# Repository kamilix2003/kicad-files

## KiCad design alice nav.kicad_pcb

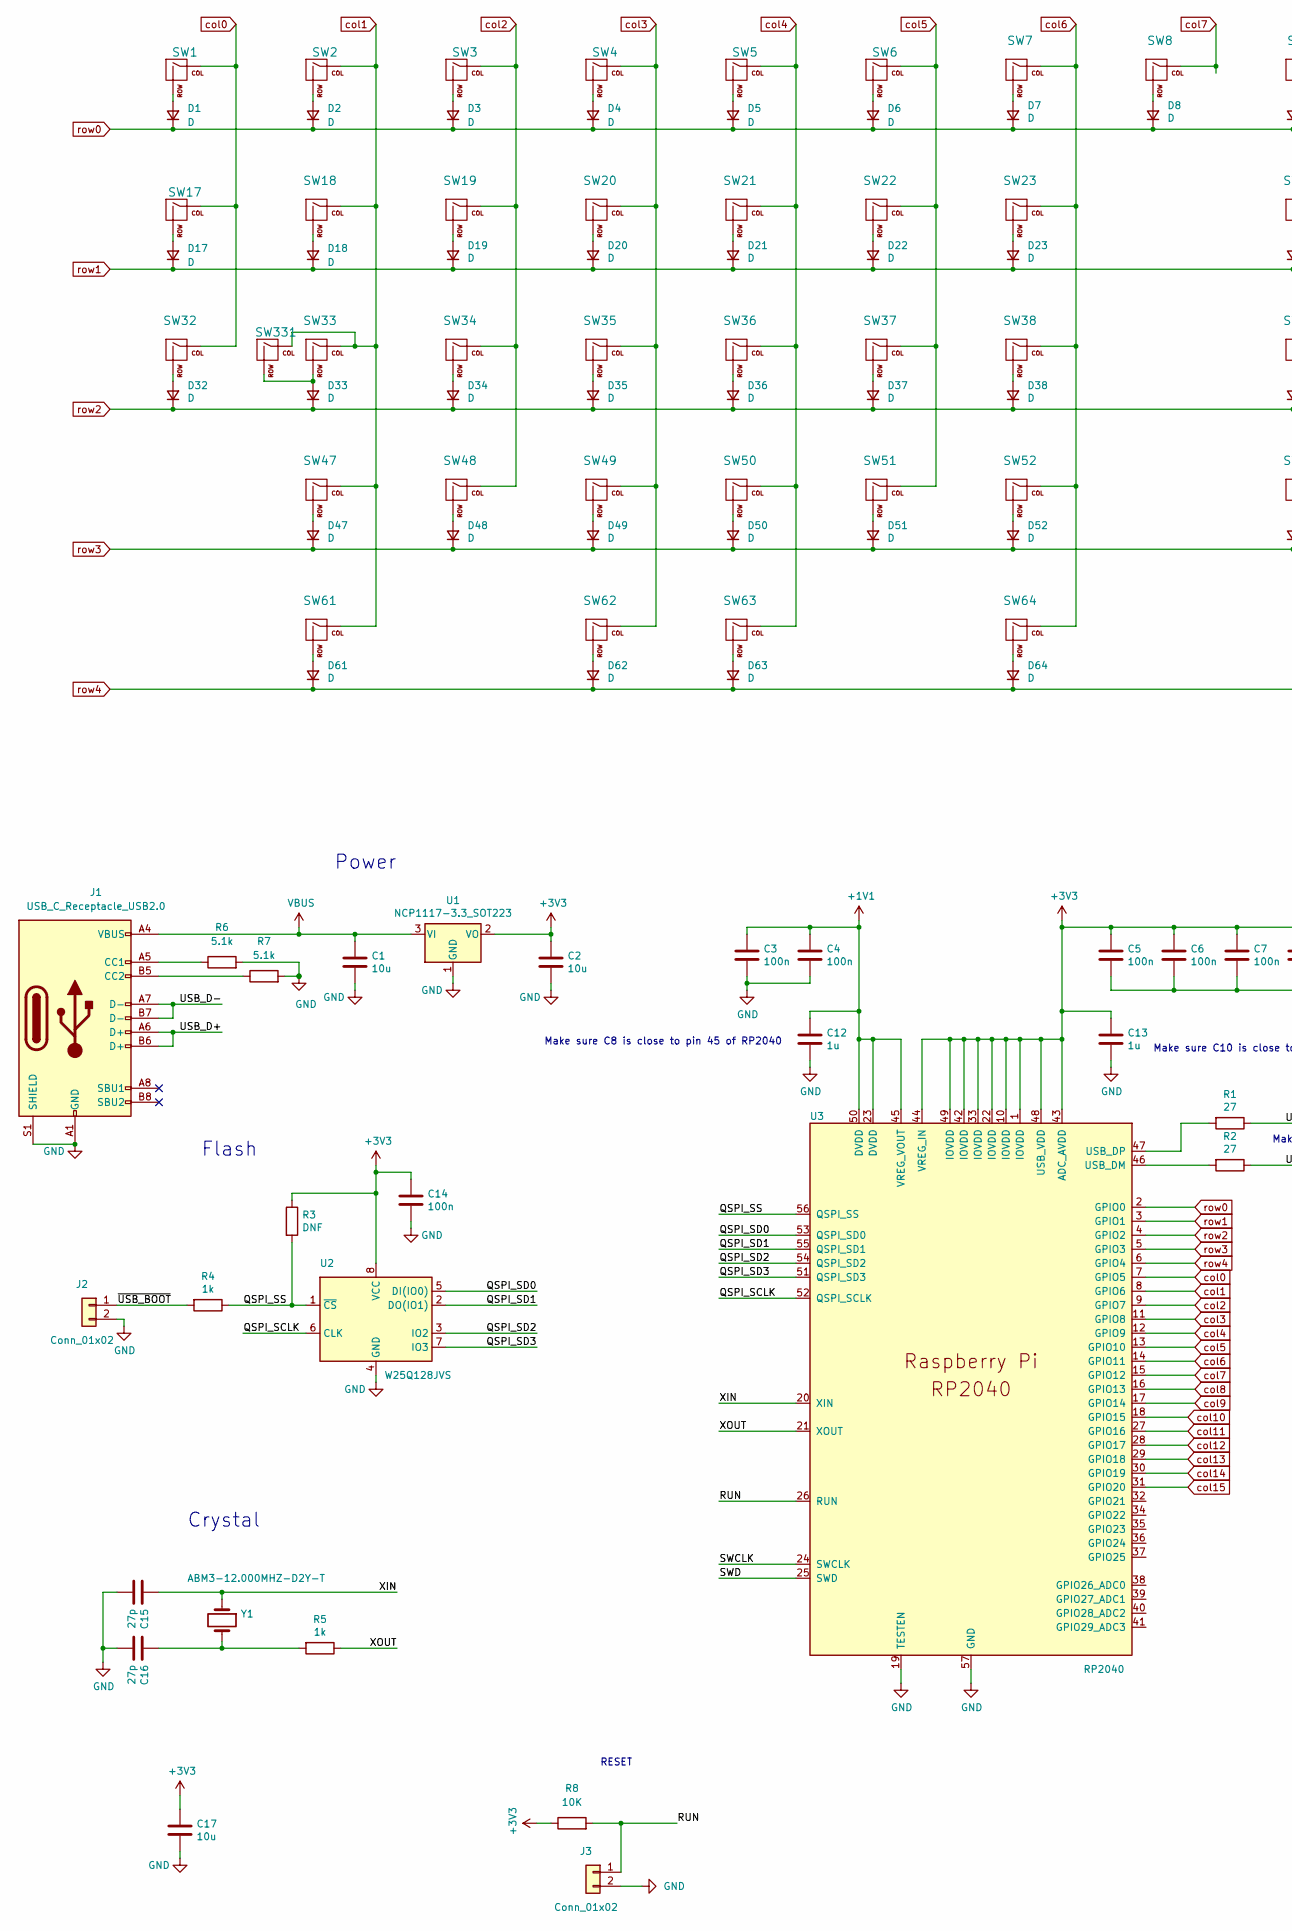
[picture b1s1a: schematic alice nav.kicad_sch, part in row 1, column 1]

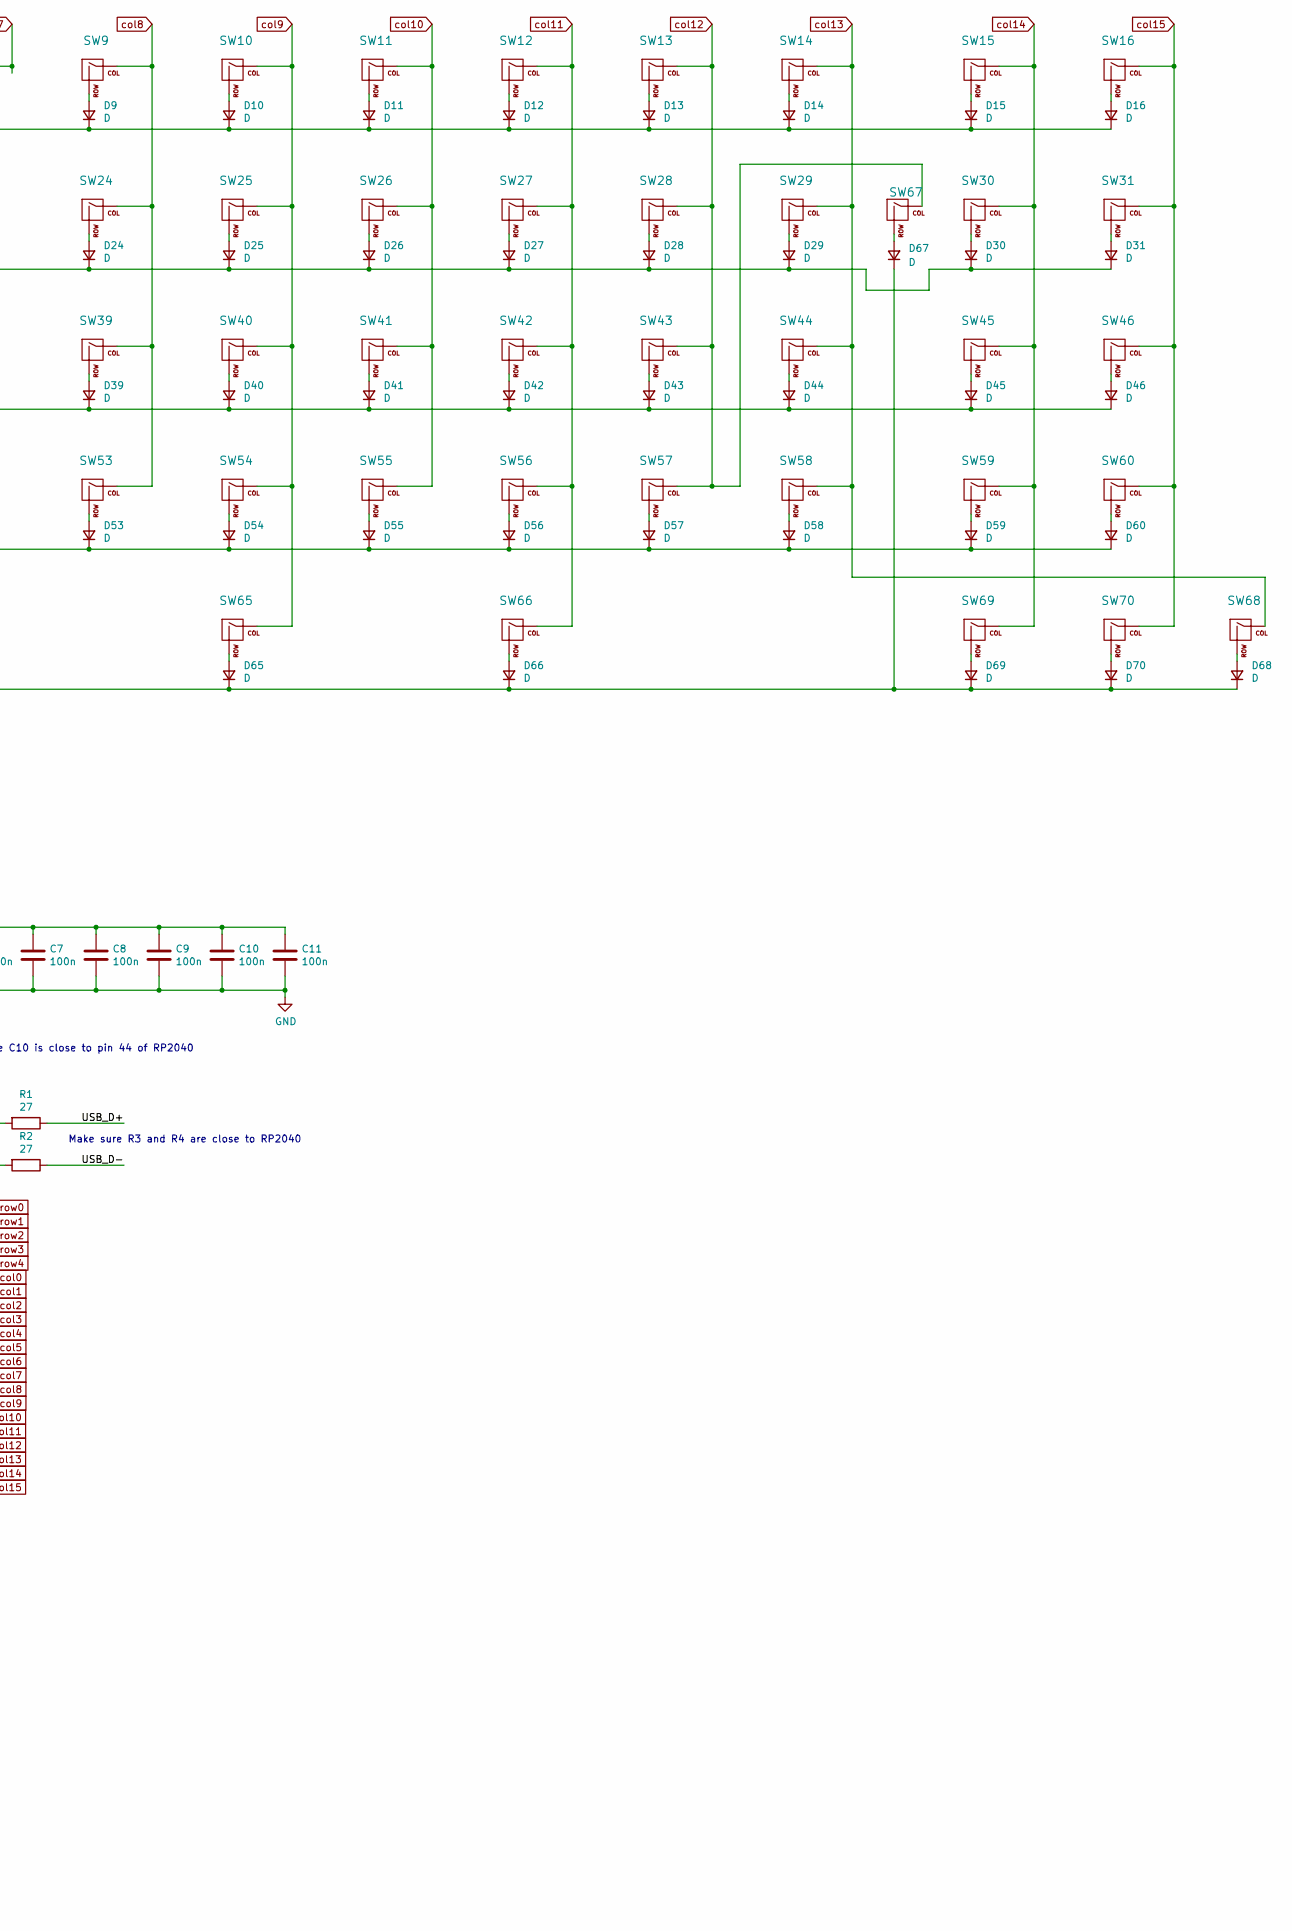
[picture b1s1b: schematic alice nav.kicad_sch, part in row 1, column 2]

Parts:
C1, C2, C17: 10u; C_0805_2012Metric
C3, C4, C5, C6, C7, C8, C9, C10, C11, C14: 100n; C_0402_1005Metric
C12, C13: 1u; C_0402_1005Metric
C15, C16: 27p; C_0402_1005Metric
D1, D2, D3, D4, D5, D6, D7, D8, D9, D10, D11, D12, D13, D14, D15, D16, D17, D18, D19, D20, D21, D22, D23, D24, D25, D26, D27, D28, D29, D30, D31, D32, D33, D34, D35, D36, D37, D38, D39, D40, D41, D42, D43, D44, D45, D46, D47, D48, D49, D50, D51, D52, D53, D54, D55, D56, D57, D58, D59, D60, D61, D62, D63, D64, D65, D66, D67, D68, D69, D70: D; D_SOD-123
J1: USB_C_Receptacle_USB2.0; TYPE-C-31-M-12
J2, J3: Conn_01x02; PinHeader_1x02_P2.54mm_Vertical
R1, R2: 27; R_0402_1005Metric
R3: DNF; R_0402_1005Metric
R4, R5: 1k; R_0402_1005Metric
R6, R7: 5.1k; R_0603_1608Metric
R8: 10K; R_0603_1608Metric
SW1, SW2, SW3, SW4, SW5, SW6, SW7, SW8, SW9, SW10, SW11, SW12, SW13, SW14, SW16, SW17, SW19, SW20, SW21, SW22, SW23, SW24, SW25, SW26, SW27, SW28, SW29, SW31, SW32, SW34, SW35, SW36, SW37, SW38, SW39, SW40, SW41, SW42, SW43, SW44, SW46, SW48, SW49, SW50, SW51, SW52, SW53, SW54, SW55, SW56, SW57, SW58, SW60, SW64, SW67, SW68, SW69, SW70: SW_Push; SW_Cherry_MX_1.00u_PCB
SW15, SW63: SW_Push; SW_Cherry_MX_2.00u_PCB
SW18, SW30, SW61, SW62, SW66: SW_Push; SW_Cherry_MX_1.50u_PCB
SW33, SW59: SW_Push; SW_Cherry_MX_1.75u_PCB
SW45, SW47: SW_Push; SW_Cherry_MX_2.25u_PCB
SW65: SW_Push; SW_Cherry_MX_2.75u_PCB
SW331: SW_Push; SW_Cherry_MX_1.25u_PCB
U1: NCP1117-3.3_SOT223; SOT-223-3_TabPin2
U2: W25Q128JVS; SOIC-8_5.23x5.23mm_P1.27mm
U3: RP2040; RP2040-QFN-56
Y1: ABM3-12.000MHZ-D2Y-T; Crystal_SMD_Abracon_ABM3-2Pin_5.0x3.2mm_HandSoldering

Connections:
+1V1: C3.1, C4.1, C12.1, U3.23 (DVDD), U3.45 (VREG_VOUT), U3.50 (DVDD)
+3V3: C2.1, C5.1, C6.1, C7.1, C8.1, C9.1, C10.1, C11.1, C13.1, C14.1, C17.1, R3.1, R8.1, U1.2 (VO), U2.8 (VCC), U3.1 (IOVDD), U3.10 (IOVDD), U3.22 (IOVDD), U3.33 (IOVDD), U3.42 (IOVDD), U3.43 (ADC_AVDD), U3.44 (VREG_IN), U3.48 (USB_VDD), U3.49 (IOVDD)
/QSPI_SCLK: U2.6 (CLK), U3.52 (QSPI_SCLK)
/QSPI_SD0: U2.5 (DI(IO0)), U3.53 (QSPI_SD0)
/QSPI_SD1: U2.2 (DO(IO1)), U3.55 (QSPI_SD1)
/QSPI_SD2: U2.3 (IO2), U3.54 (QSPI_SD2)
/QSPI_SD3: U2.7 (IO3), U3.51 (QSPI_SD3)
/QSPI_SS: R3.2, R4.1, U2.1 (~CS), U3.56 (QSPI_SS)
/RUN: J3.1, R8.2, U3.26 (RUN)
/SWCLK: U3.24 (SWCLK)
/SWD: U3.25 (SWD)
/USB_D+: J1.A6 (D+), J1.B6 (D+), R1.1
/USB_D-: J1.A7 (D-), J1.B7 (D-), R2.1
/XIN: C15.1, U3.20 (XIN), Y1.1
/XOUT: R5.1, U3.21 (XOUT)
/~USB_BOOT: J2.1, R4.2
GND: C1.2, C2.2, C3.2, C4.2, C5.2, C6.2, C7.2, C8.2, C9.2, C10.2, C11.2, C12.2, C13.2, C14.2, C15.2, C16.2, C17.2, J1.A1 (GND), J1.A12 (GND), J1.B1 (GND), J1.B12 (GND), J1.S1 (SHIELD), J2.2, J3.2, R6.2, R7.2, U1.1 (GND), U2.4 (GND), U3.19 (TESTEN), U3.57 (GND)
unnamed: C16.1, R5.2, Y1.2
unnamed: D1.2 (A), SW1.2 (ROW)
unnamed: D2.2 (A), SW2.2 (ROW)
unnamed: D3.2 (A), SW3.2 (ROW)
unnamed: D4.2 (A), SW4.2 (ROW)
unnamed: D5.2 (A), SW5.2 (ROW)
unnamed: D6.2 (A), SW6.2 (ROW)
unnamed: D7.2 (A), SW7.2 (ROW)
unnamed: D8.2 (A), SW8.2 (ROW)
unnamed: D9.2 (A), SW9.2 (ROW)
unnamed: D10.2 (A), SW10.2 (ROW)
unnamed: D11.2 (A), SW11.2 (ROW)
unnamed: D12.2 (A), SW12.2 (ROW)
unnamed: D13.2 (A), SW13.2 (ROW)
unnamed: D14.2 (A), SW14.2 (ROW)
unnamed: D15.2 (A), SW15.2 (ROW)
unnamed: D16.2 (A), SW16.2 (ROW)
unnamed: D17.2 (A), SW17.2 (ROW)
unnamed: D18.2 (A), SW18.2 (ROW)
unnamed: D19.2 (A), SW19.2 (ROW)
unnamed: D20.2 (A), SW20.2 (ROW)
unnamed: D21.2 (A), SW21.2 (ROW)
unnamed: D22.2 (A), SW22.2 (ROW)
unnamed: D23.2 (A), SW23.2 (ROW)
unnamed: D24.2 (A), SW24.2 (ROW)
unnamed: D25.2 (A), SW25.2 (ROW)
unnamed: D26.2 (A), SW26.2 (ROW)
unnamed: D27.2 (A), SW27.2 (ROW)
unnamed: D28.2 (A), SW28.2 (ROW)
unnamed: D29.2 (A), SW29.2 (ROW)
unnamed: D30.2 (A), SW30.2 (ROW)
unnamed: D31.2 (A), SW31.2 (ROW)
unnamed: D32.2 (A), SW32.2 (ROW)
unnamed: D33.2 (A), SW33.2 (ROW), SW331.2 (ROW)
unnamed: D34.2 (A), SW34.2 (ROW)
unnamed: D35.2 (A), SW35.2 (ROW)
unnamed: D36.2 (A), SW36.2 (ROW)
unnamed: D37.2 (A), SW37.2 (ROW)
unnamed: D38.2 (A), SW38.2 (ROW)
unnamed: D39.2 (A), SW39.2 (ROW)
unnamed: D40.2 (A), SW40.2 (ROW)
unnamed: D41.2 (A), SW41.2 (ROW)
unnamed: D42.2 (A), SW42.2 (ROW)
unnamed: D43.2 (A), SW43.2 (ROW)
unnamed: D44.2 (A), SW44.2 (ROW)
unnamed: D45.2 (A), SW45.2 (ROW)
unnamed: D46.2 (A), SW46.2 (ROW)
unnamed: D47.2 (A), SW47.2 (ROW)
unnamed: D48.2 (A), SW48.2 (ROW)
unnamed: D49.2 (A), SW49.2 (ROW)
unnamed: D50.2 (A), SW50.2 (ROW)
unnamed: D51.2 (A), SW51.2 (ROW)
unnamed: D52.2 (A), SW52.2 (ROW)
unnamed: D53.2 (A), SW53.2 (ROW)
unnamed: D54.2 (A), SW54.2 (ROW)
unnamed: D55.2 (A), SW55.2 (ROW)
unnamed: D56.2 (A), SW56.2 (ROW)
unnamed: D57.2 (A), SW57.2 (ROW)
unnamed: D58.2 (A), SW58.2 (ROW)
unnamed: D59.2 (A), SW59.2 (ROW)
unnamed: D60.2 (A), SW60.2 (ROW)
unnamed: D61.2 (A), SW61.2 (ROW)
unnamed: D62.2 (A), SW62.2 (ROW)
unnamed: D63.2 (A), SW63.2 (ROW)
unnamed: D64.2 (A), SW64.2 (ROW)
unnamed: D65.2 (A), SW65.2 (ROW)
unnamed: D66.2 (A), SW66.2 (ROW)
unnamed: D67.2 (A), SW67.2 (ROW)
unnamed: D68.2 (A), SW68.2 (ROW)
unnamed: D69.2 (A), SW69.2 (ROW)
unnamed: D70.2 (A), SW70.2 (ROW)
unnamed: J1.A5 (CC1), R6.1
unnamed: J1.B5 (CC2), R7.1
unnamed: R1.2, U3.47 (USB_DP)
unnamed: R2.2, U3.46 (USB_DM)
VBUS: C1.1, J1.A4 (VBUS), J1.A9 (VBUS), J1.B4 (VBUS), J1.B9 (VBUS), U1.3 (VI)
col0: SW1.1 (COL), SW17.1 (COL), SW32.1 (COL), U3.7 (GPIO5)
col1: SW2.1 (COL), SW18.1 (COL), SW33.1 (COL), SW47.1 (COL), SW61.1 (COL), SW331.1 (COL), U3.8 (GPIO6)
col2: SW3.1 (COL), SW19.1 (COL), SW34.1 (COL), SW48.1 (COL), U3.9 (GPIO7)
col3: SW4.1 (COL), SW20.1 (COL), SW35.1 (COL), SW49.1 (COL), SW62.1 (COL), U3.11 (GPIO8)
col4: SW5.1 (COL), SW21.1 (COL), SW36.1 (COL), SW50.1 (COL), SW63.1 (COL), U3.12 (GPIO9)
col5: SW6.1 (COL), SW22.1 (COL), SW37.1 (COL), SW51.1 (COL), U3.13 (GPIO10)
col6: SW7.1 (COL), SW23.1 (COL), SW38.1 (COL), SW52.1 (COL), SW64.1 (COL), U3.14 (GPIO11)
col7: SW8.1 (COL), U3.15 (GPIO12)
col8: SW9.1 (COL), SW24.1 (COL), SW39.1 (COL), SW53.1 (COL), U3.16 (GPIO13)
col9: SW10.1 (COL), SW25.1 (COL), SW40.1 (COL), SW54.1 (COL), SW65.1 (COL), U3.17 (GPIO14)
col10: SW11.1 (COL), SW26.1 (COL), SW41.1 (COL), SW55.1 (COL), U3.18 (GPIO15)
col11: SW12.1 (COL), SW27.1 (COL), SW42.1 (COL), SW56.1 (COL), SW66.1 (COL), U3.27 (GPIO16)
col12: SW13.1 (COL), SW28.1 (COL), SW43.1 (COL), SW57.1 (COL), SW67.1 (COL), U3.28 (GPIO17)
col13: SW14.1 (COL), SW29.1 (COL), SW44.1 (COL), SW58.1 (COL), SW68.1 (COL), U3.29 (GPIO18)
col14: SW15.1 (COL), SW30.1 (COL), SW45.1 (COL), SW59.1 (COL), SW69.1 (COL), U3.30 (GPIO19)
col15: SW16.1 (COL), SW31.1 (COL), SW46.1 (COL), SW60.1 (COL), SW70.1 (COL), U3.31 (GPIO20)
row0: D1.1 (K), D2.1 (K), D3.1 (K), D4.1 (K), D5.1 (K), D6.1 (K), D7.1 (K), D8.1 (K), D9.1 (K), D10.1 (K), D11.1 (K), D12.1 (K), D13.1 (K), D14.1 (K), D15.1 (K), D16.1 (K), U3.2 (GPIO0)
row1: D17.1 (K), D18.1 (K), D19.1 (K), D20.1 (K), D21.1 (K), D22.1 (K), D23.1 (K), D24.1 (K), D25.1 (K), D26.1 (K), D27.1 (K), D28.1 (K), D29.1 (K), D30.1 (K), D31.1 (K), U3.3 (GPIO1)
row2: D32.1 (K), D33.1 (K), D34.1 (K), D35.1 (K), D36.1 (K), D37.1 (K), D38.1 (K), D39.1 (K), D40.1 (K), D41.1 (K), D42.1 (K), D43.1 (K), D44.1 (K), D45.1 (K), D46.1 (K), U3.4 (GPIO2)
row3: D47.1 (K), D48.1 (K), D49.1 (K), D50.1 (K), D51.1 (K), D52.1 (K), D53.1 (K), D54.1 (K), D55.1 (K), D56.1 (K), D57.1 (K), D58.1 (K), D59.1 (K), D60.1 (K), U3.5 (GPIO3)
row4: D61.1 (K), D62.1 (K), D63.1 (K), D64.1 (K), D65.1 (K), D66.1 (K), D67.1 (K), D68.1 (K), D69.1 (K), D70.1 (K), U3.6 (GPIO4)

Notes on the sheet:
Make sure C10 is close to pin 44 of RP2040
Make sure C8 is close to pin 45 of RP2040
RESET
Flash
Power
Make sure R3 and R4 are close to RP2040
Crystal

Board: 2 copper layers, 173 parts (102 on the bottom side), 112 nets, no tracks yet.
